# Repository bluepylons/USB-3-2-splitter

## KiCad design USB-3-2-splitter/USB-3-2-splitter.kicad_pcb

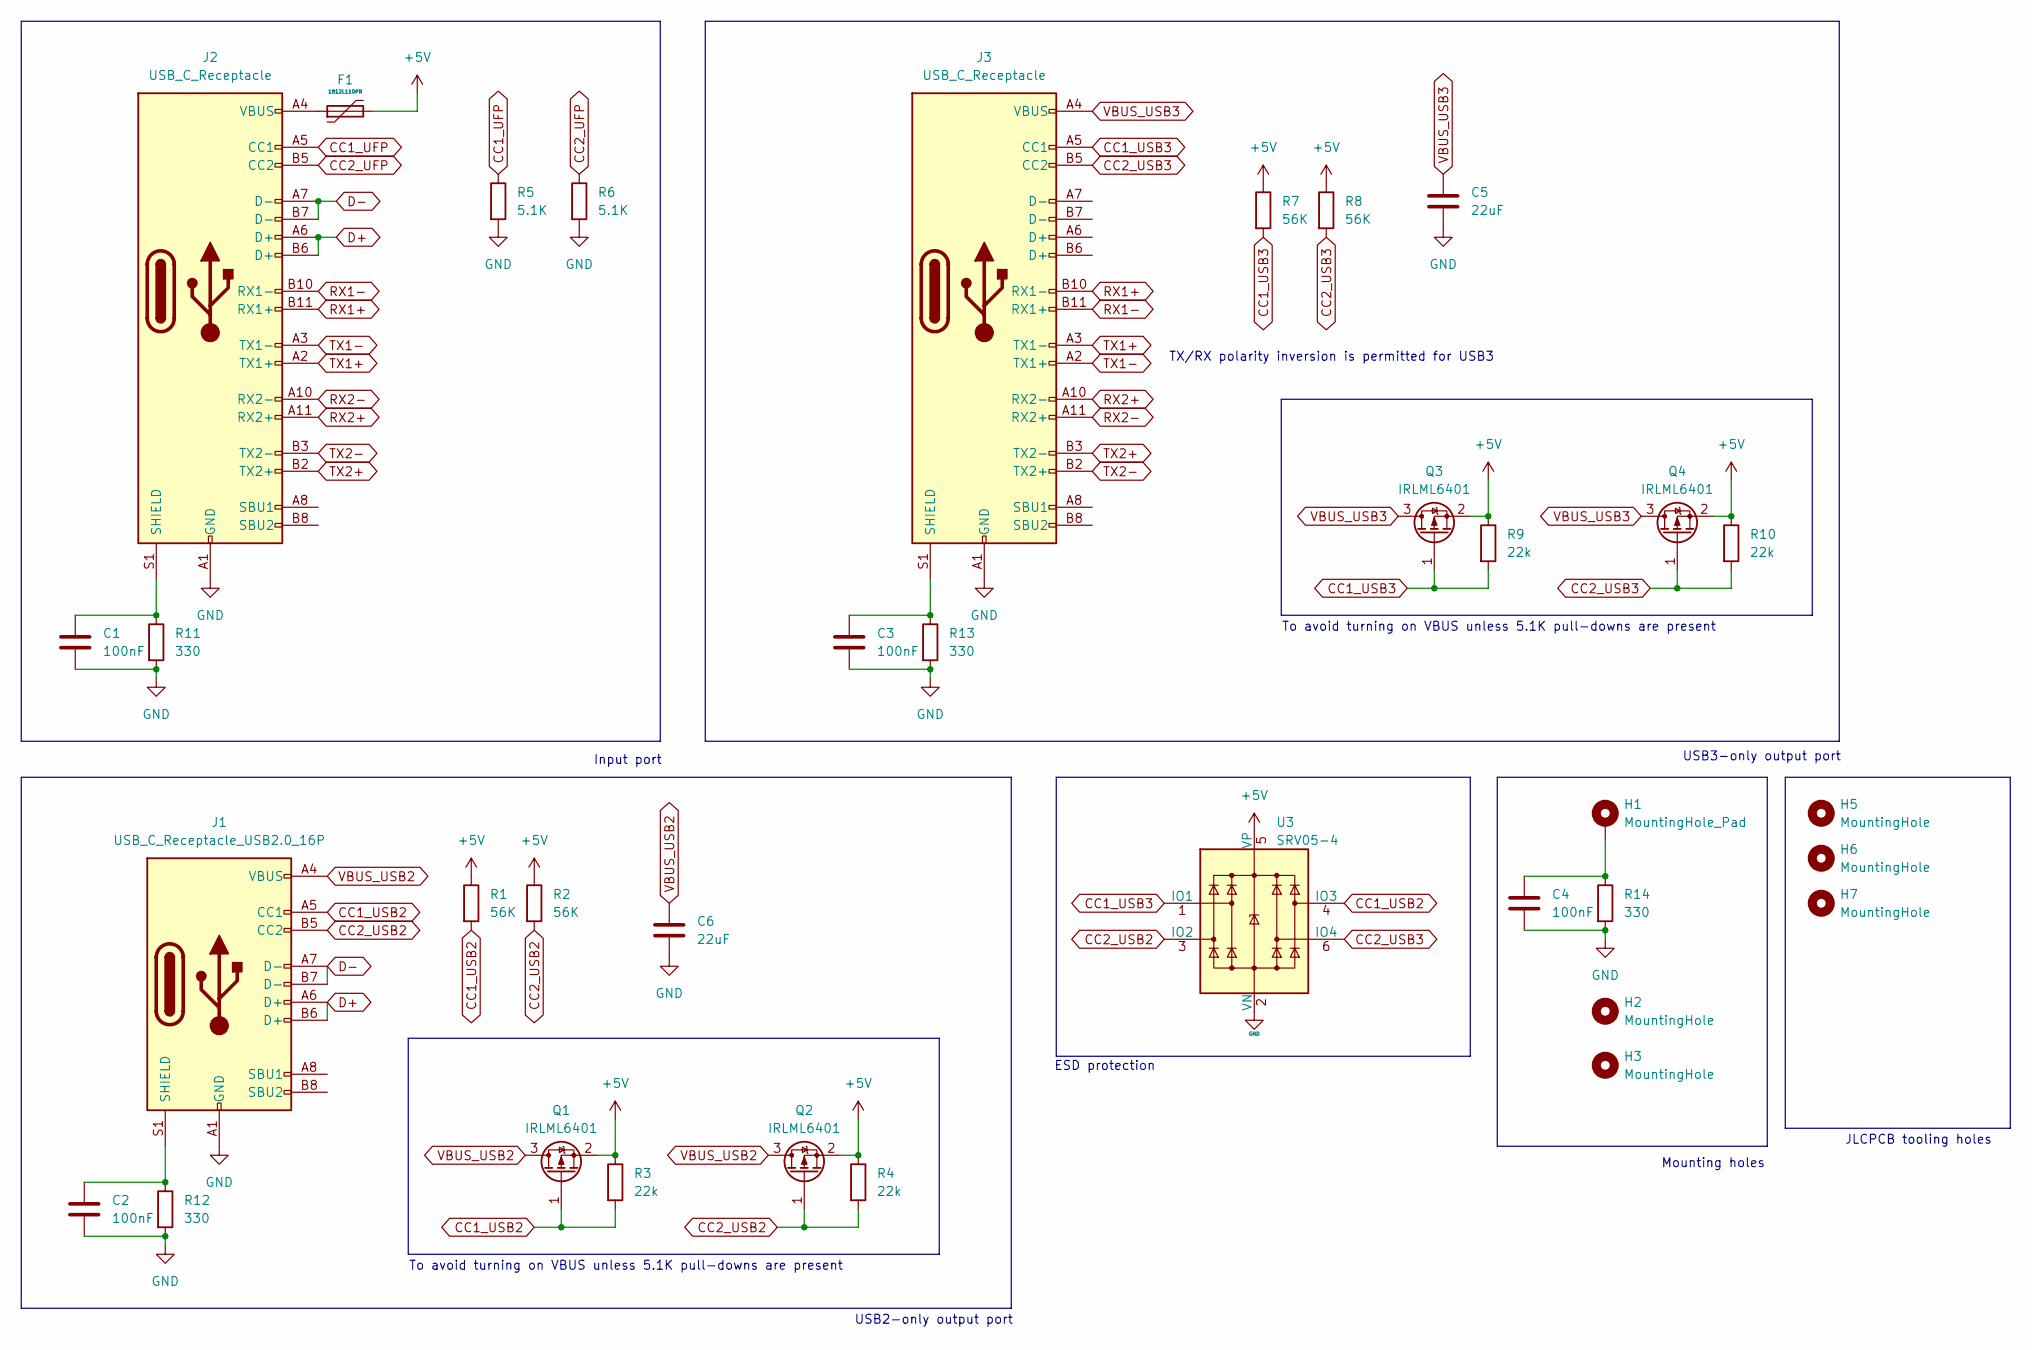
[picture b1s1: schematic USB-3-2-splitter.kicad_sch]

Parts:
C1, C2, C3, C4: 100nF; C_0805_2012Metric_Pad1.18x1.45mm_HandSolder
C5, C6: 22uF; C_1206_3216Metric_Pad1.33x1.80mm_HandSolder
F1: 1812L110PR; Fuse_1812_4532Metric_Pad1.30x3.40mm_HandSolder; Manufacturer Part No ASMD1206-150; LCSC Part No C135342
H1: MountingHole_Pad; MountingHole_3.2mm_M3_ISO7380_Pad
H2, H3: MountingHole; MountingHole_3.2mm_M3_ISO7380
H5, H6, H7: MountingHole; JLCPCB-tooling-hole
J1: USB_C_Receptacle_USB2.0_16P; USB_C_Receptacle_HRO_TYPE-C-31-M-12
J2, J3: USB_C_Receptacle; USB_C_Receptacle_Amphenol_12401610E4-2A_CircularHoles
Q1, Q2, Q3, Q4: IRLML6401; SOT-23
R1, R2, R7, R8: 56K; R_0805_2012Metric_Pad1.20x1.40mm_HandSolder
R3, R4, R9, R10: 22k; R_0805_2012Metric_Pad1.20x1.40mm_HandSolder
R5, R6: 5.1K; R_0805_2012Metric_Pad1.20x1.40mm_HandSolder
R11, R12, R13, R14: 330; R_0805_2012Metric_Pad1.20x1.40mm_HandSolder
U3: SRV05-4; SOT-23-6

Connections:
+5V: F1.2, Q1.2 (S), Q2.2 (S), Q3.2 (S), Q4.2 (S), R1.1, R2.1, R3.1, R4.1, R7.1, R8.1, R9.1, R10.1, U3.5 (VP)
CC1_UFP: J2.A5 (CC1), R5.1
CC1_USB2: J1.A5 (CC1), Q1.1 (G), R1.2, R3.2, U3.4 (IO3)
CC1_USB3: J3.A5 (CC1), Q3.1 (G), R7.2, R9.2, U3.1 (IO1)
CC2_UFP: J2.B5 (CC2), R6.1
CC2_USB2: J1.B5 (CC2), Q2.1 (G), R2.2, R4.2, U3.3 (IO2)
CC2_USB3: J3.B5 (CC2), Q4.1 (G), R8.2, R10.2, U3.6 (IO4)
D+: J1.A6 (D+), J1.B6 (D+), J2.A6 (D+), J2.B6 (D+)
D-: J1.A7 (D-), J1.B7 (D-), J2.A7 (D-), J2.B7 (D-)
GND: C1.2, C2.2, C3.2, C4.2, C5.2, C6.2, J1.A1 (GND), J1.A12 (GND), J1.B1 (GND), J1.B12 (GND), J2.A1 (GND), J2.A12 (GND), J2.B1 (GND), J2.B12 (GND), J3.A1 (GND), J3.A12 (GND), J3.B1 (GND), J3.B12 (GND), R5.2, R6.2, R11.2, R12.2, R13.2, R14.2, U3.2 (VN)
unnamed: C4.1, H1.1, R14.1
unnamed: F1.1, J2.A4 (VBUS), J2.A9 (VBUS), J2.B4 (VBUS), J2.B9 (VBUS)
unnamed: C2.1, J1.S1 (SHIELD), R12.1
unnamed: C1.1, J2.S1 (SHIELD), R11.1
unnamed: C3.1, J3.S1 (SHIELD), R13.1
RX1+: J2.B11 (RX1+), J3.B10 (RX1-)
RX1-: J2.B10 (RX1-), J3.B11 (RX1+)
RX2+: J2.A11 (RX2+), J3.A10 (RX2-)
RX2-: J2.A10 (RX2-), J3.A11 (RX2+)
TX1+: J2.A2 (TX1+), J3.A3 (TX1-)
TX1-: J2.A3 (TX1-), J3.A2 (TX1+)
TX2+: J2.B2 (TX2+), J3.B3 (TX2-)
TX2-: J2.B3 (TX2-), J3.B2 (TX2+)
VBUS_USB2: C6.1, J1.A4 (VBUS), J1.A9 (VBUS), J1.B4 (VBUS), J1.B9 (VBUS), Q1.3 (D), Q2.3 (D)
VBUS_USB3: C5.1, J3.A4 (VBUS), J3.A9 (VBUS), J3.B4 (VBUS), J3.B9 (VBUS), Q3.3 (D), Q4.3 (D)

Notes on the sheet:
JLCPCB tooling holes
Input port
To avoid turning on VBUS unless 5.1K pull-downs are present
TX/RX polarity inversion is permitted for USB3
ESD protection
USB3-only output port
Mounting holes
USB2-only output port

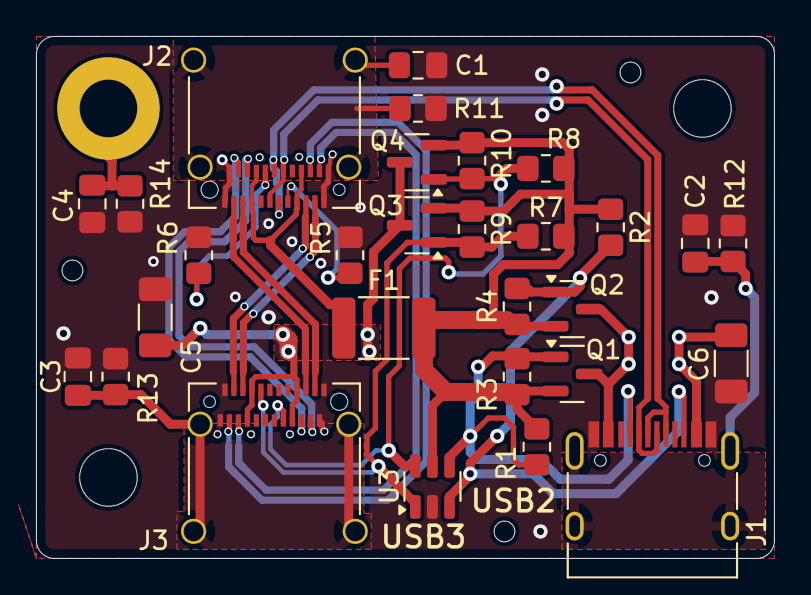
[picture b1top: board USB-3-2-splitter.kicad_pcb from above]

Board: 4 copper layers, 41.0 x 29.0 mm, 35 parts (0 on the bottom side), 25 nets.

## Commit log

2025-04-14 Ran DRC
2025-04-14 Manufacturing files
2025-04-14 More adjustments
